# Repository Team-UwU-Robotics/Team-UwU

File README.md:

# Team-UwU
Official Repository for Team UwU

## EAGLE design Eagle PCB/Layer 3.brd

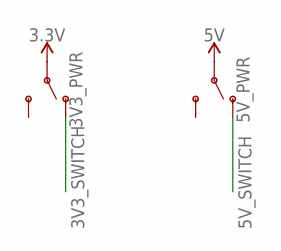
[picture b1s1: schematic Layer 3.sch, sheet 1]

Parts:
3V3_PWR, 5V_PWR: SWITCH-SPDT-PTH-11.6X4.0MM-LOCK; SWITCH_SPDT_PTH_11.6X4.0MM_LOCK

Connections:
3.3V: 3V3_PWR.2; also elsewhere on the board
3V3_SWITCH: 3V3_PWR.1 (O); also elsewhere on the board
5V_SWITCH: 5V_PWR.1 (O); also elsewhere on the board

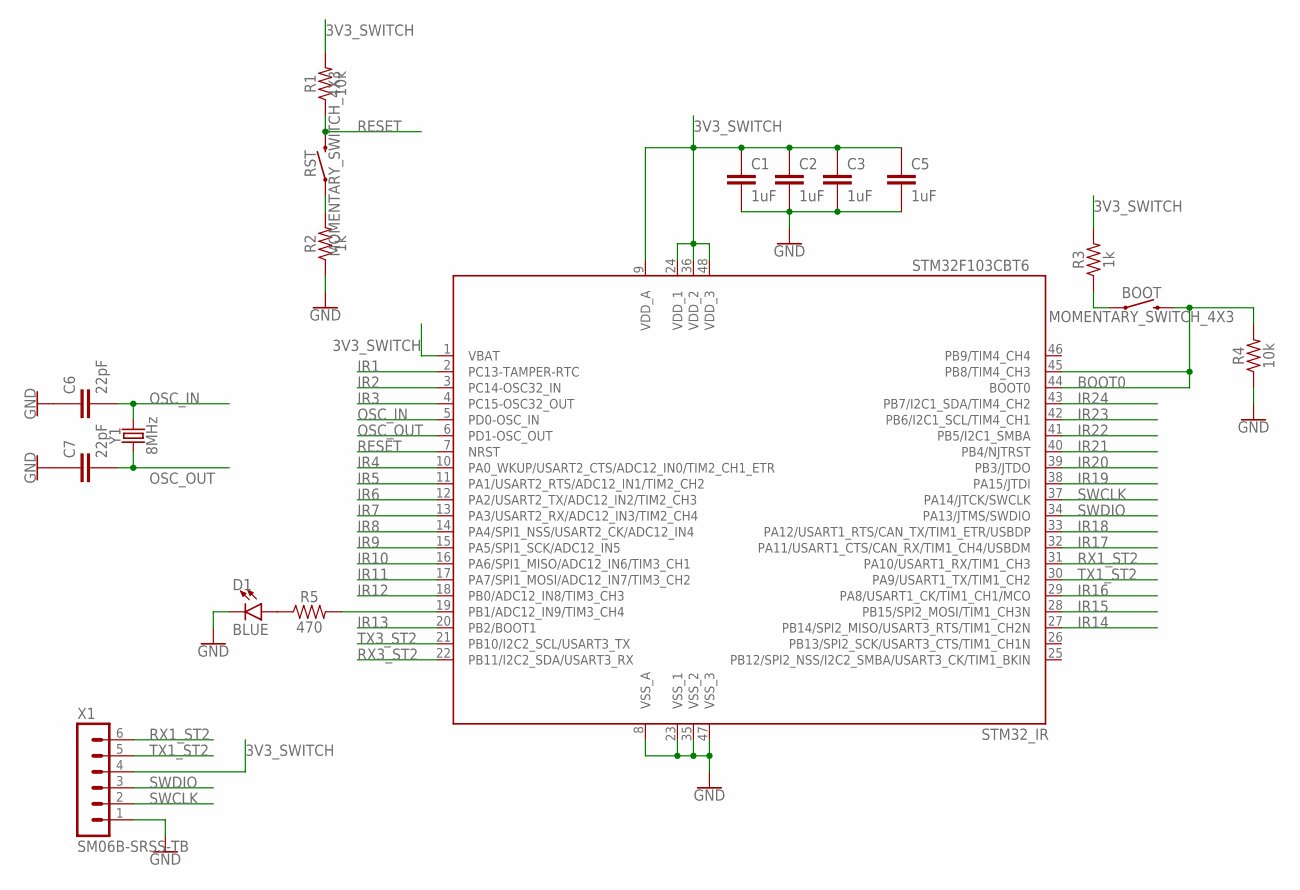
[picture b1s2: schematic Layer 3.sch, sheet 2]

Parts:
BOOT: MOMENTARY_SWITCH_4X3
C1, C2, C3, C5: 1uF; C0603
C6, C7: 22pF; C0603
D1: BLUE; LED-0603
R1, R4: 10k; R0603
R2, R3: 1k; R0603
R5: 470; R0603
RST: MOMENTARY_SWITCH_4X3
STM32_IR: STM32F103CBT6; LQFP48
X1: SM06B-SRSS-TB
Y1: 8MHz; CRYSTAL-SMD-5X3.2-2PAD

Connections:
3V3_SWITCH: C1.1, C2.1, C3.1, C5.2, R1.2, R3.2, STM32_IR.1 (VBAT), STM32_IR.9 (VDD_A), STM32_IR.24 (VDD_1), STM32_IR.36 (VDD_2), STM32_IR.48 (VDD_3), X1.4; also elsewhere on the board
BOOT0: BOOT.P$2 (2), R4.2, STM32_IR.44 (BOOT0), STM32_IR.45 (PB8/TIM4_CH3)
GND: C1.2, C2.2, C3.2, C5.1, C6.1, C7.1, D1.C, R2.1, R4.1, STM32_IR.8 (VSS_A), STM32_IR.23 (VSS_1), STM32_IR.35 (VSS_2), STM32_IR.47 (VSS_3), X1.1; also elsewhere on the board
IR1: STM32_IR.2 (PC13-TAMPER-RTC); also elsewhere on the board
IR2: STM32_IR.3 (PC14-OSC32_IN); also elsewhere on the board
IR3: STM32_IR.4 (PC15-OSC32_OUT); also elsewhere on the board
IR4: STM32_IR.10 (PA0_WKUP/USART2_CTS/ADC12_IN0/TIM2_CH1_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); also elsewhere on the board
IR5: STM32_IR.11 (PA1/USART2_RTS/ADC12_IN1/TIM2_CH2); also elsewhere on the board
IR6: STM32_IR.12 (PA2/USART2_TX/ADC12_IN2/TIM2_CH3); also elsewhere on the board
IR7: STM32_IR.13 (PA3/USART2_RX/ADC12_IN3/TIM2_CH4); also elsewhere on the board
IR8: STM32_IR.14 (PA4/SPI1_NSS/USART2_CK/ADC12_IN4); also elsewhere on the board
IR9: STM32_IR.15 (PA5/SPI1_SCK/ADC12_IN5); also elsewhere on the board
IR10: STM32_IR.16 (PA6/SPI1_MISO/ADC12_IN6/TIM3_CH1); also elsewhere on the board
IR11: STM32_IR.17 (PA7/SPI1_MOSI/ADC12_IN7/TIM3_CH2); also elsewhere on the board
IR12: STM32_IR.18 (PB0/ADC12_IN8/TIM3_CH3); also elsewhere on the board
IR13: STM32_IR.20 (PB2/BOOT1); also elsewhere on the board
IR14: STM32_IR.27 (PB14/SPI2_MISO/USART3_RTS/TIM1_CH2N); also elsewhere on the board
IR15: STM32_IR.28 (PB15/SPI2_MOSI/TIM1_CH3N); also elsewhere on the board
IR16: STM32_IR.29 (PA8/USART1_CK/TIM1_CH1/MCO); also elsewhere on the board
IR17: STM32_IR.32 (PA11/USART1_CTS/CAN_RX/TIM1_CH4/USBDM); also elsewhere on the board
IR18: STM32_IR.33 (PA12/USART1_RTS/CAN_TX/TIM1_ETR/USBDP); also elsewhere on the board
IR19: STM32_IR.38 (PA15/JTDI); also elsewhere on the board
IR20: STM32_IR.39 (PB3/JTDO); also elsewhere on the board
IR21: STM32_IR.40 (PB4/NJTRST); also elsewhere on the board
IR22: STM32_IR.41 (PB5/I2C1_SMBA); also elsewhere on the board
IR23: STM32_IR.42 (PB6/I2C1_SCL/TIM4_CH1); also elsewhere on the board
IR24: STM32_IR.43 (PB7/I2C1_SDA/TIM4_CH2); also elsewhere on the board
unnamed: R2.2, RST.P$1 (1)
unnamed: BOOT.P$1 (1), R3.1
unnamed: R5.2, STM32_IR.19 (PB1/ADC12_IN9/TIM3_CH4)
unnamed: D1.A, R5.1
OSC_IN: C6.2, STM32_IR.5 (PD0-OSC_IN), Y1.P$2 (2)
OSC_OUT: C7.2, STM32_IR.6 (PD1-OSC_OUT), Y1.P$1 (1)
RESET: R1.1, RST.P$2 (2), STM32_IR.7 (NRST)
RX1_ST2: STM32_IR.31 (PA10/USART1_RX/TIM1_CH3), X1.6; also elsewhere on the board
RX3_ST2: STM32_IR.22 (PB11/I2C2_SDA/USART3_RX)
SWCLK: STM32_IR.37 (PA14/JTCK/SWCLK), X1.2
SWDIO: STM32_IR.34 (PA13/JTMS/SWDIO), X1.3
TX1_ST2: STM32_IR.30 (PA9/USART1_TX/TIM1_CH2), X1.5; also elsewhere on the board
TX3_ST2: STM32_IR.21 (PB10/I2C2_SCL/USART3_TX)

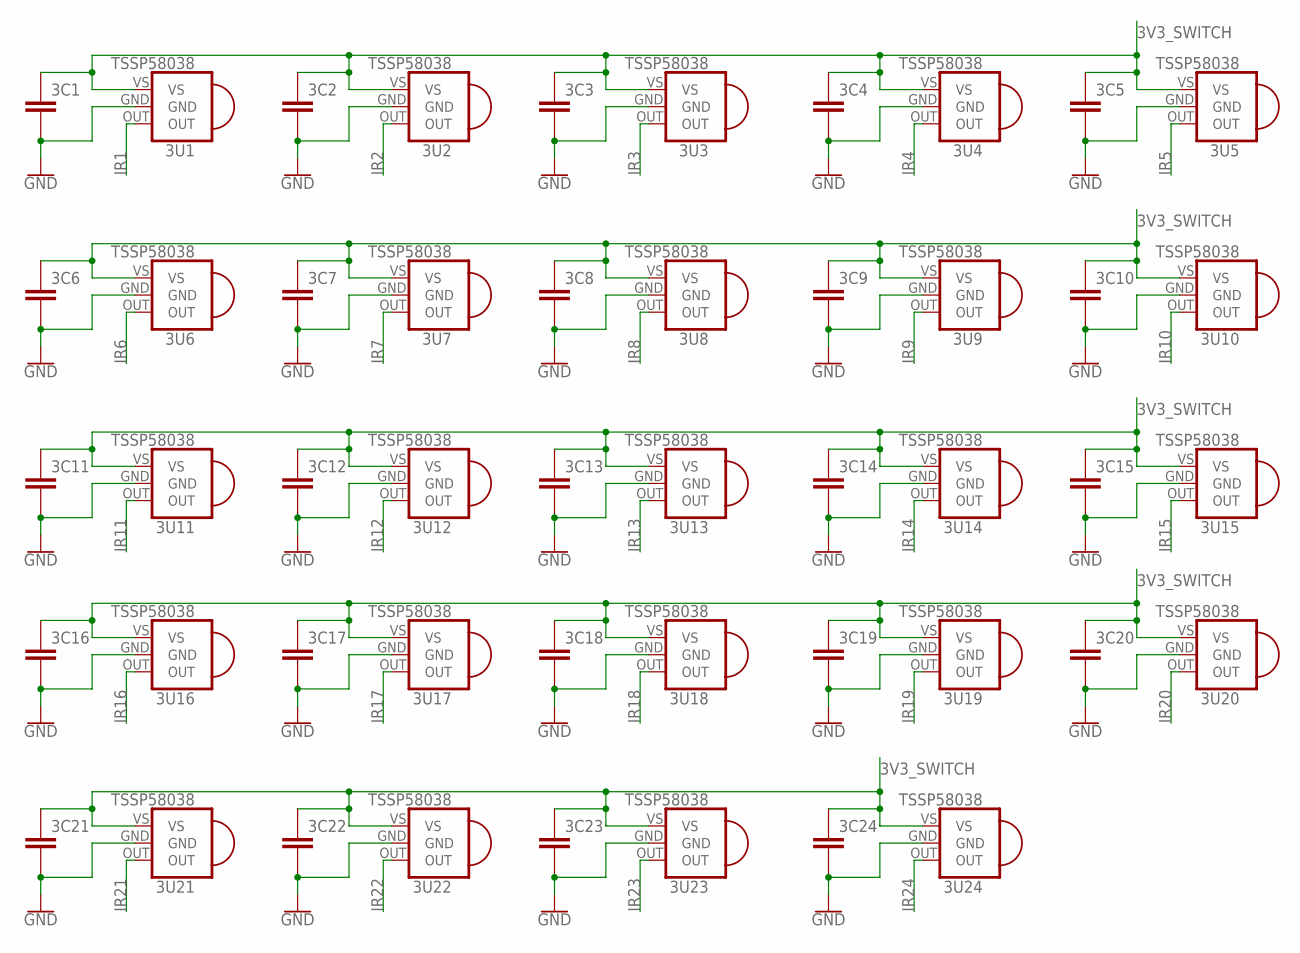
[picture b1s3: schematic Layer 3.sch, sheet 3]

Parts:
3C1, 3C2, 3C3, 3C4, 3C5, 3C6, 3C7, 3C8, 3C9, 3C10, 3C11, 3C12, 3C13, 3C14, 3C15, 3C16, 3C17, 3C18, 3C19, 3C20, 3C21, 3C22, 3C23, 3C24: CAPACITOR0603; C0603
3U1, 3U2, 3U3, 3U4, 3U5, 3U6, 3U7, 3U8, 3U9, 3U10, 3U11, 3U12, 3U13, 3U14, 3U15, 3U16, 3U17, 3U18, 3U19, 3U20, 3U21, 3U22, 3U23, 3U24: TSSP58038

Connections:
3V3_SWITCH: 3C1.1, 3C2.1, 3C3.1, 3C4.1, 3C5.1, 3C6.1, 3C7.1, 3C8.1, 3C9.1, 3C10.1, 3C11.1, 3C12.1, 3C13.1, 3C14.1, 3C15.1, 3C16.1, 3C17.1, 3C18.1, 3C19.1, 3C20.1, 3C21.1, 3C22.1, 3C23.1, 3C24.1, 3U1.VS, 3U2.VS, 3U3.VS, 3U4.VS, 3U5.VS, 3U6.VS, 3U7.VS, 3U8.VS, 3U9.VS, 3U10.VS, 3U11.VS, 3U12.VS, 3U13.VS, 3U14.VS, 3U15.VS, 3U16.VS, 3U17.VS, 3U18.VS, 3U19.VS, 3U20.VS, 3U21.VS, 3U22.VS, 3U23.VS, 3U24.VS; also elsewhere on the board
GND: 3C1.2, 3C2.2, 3C3.2, 3C4.2, 3C5.2, 3C6.2, 3C7.2, 3C8.2, 3C9.2, 3C10.2, 3C11.2, 3C12.2, 3C13.2, 3C14.2, 3C15.2, 3C16.2, 3C17.2, 3C18.2, 3C19.2, 3C20.2, 3C21.2, 3C22.2, 3C23.2, 3C24.2, 3U1.GND, 3U2.GND, 3U3.GND, 3U4.GND, 3U5.GND, 3U6.GND, 3U7.GND, 3U8.GND, 3U9.GND, 3U10.GND, 3U11.GND, 3U12.GND, 3U13.GND, 3U14.GND, 3U15.GND, 3U16.GND, 3U17.GND, 3U18.GND, 3U19.GND, 3U20.GND, 3U21.GND, 3U22.GND, 3U23.GND, 3U24.GND; also elsewhere on the board
IR1: 3U1.OUT; also elsewhere on the board
IR2: 3U2.OUT; also elsewhere on the board
IR3: 3U3.OUT; also elsewhere on the board
IR4: 3U4.OUT; also elsewhere on the board
IR5: 3U5.OUT; also elsewhere on the board
IR6: 3U6.OUT; also elsewhere on the board
IR7: 3U7.OUT; also elsewhere on the board
IR8: 3U8.OUT; also elsewhere on the board
IR9: 3U9.OUT; also elsewhere on the board
IR10: 3U10.OUT; also elsewhere on the board
IR11: 3U11.OUT; also elsewhere on the board
IR12: 3U12.OUT; also elsewhere on the board
IR13: 3U13.OUT; also elsewhere on the board
IR14: 3U14.OUT; also elsewhere on the board
IR15: 3U15.OUT; also elsewhere on the board
IR16: 3U16.OUT; also elsewhere on the board
IR17: 3U17.OUT; also elsewhere on the board
IR18: 3U18.OUT; also elsewhere on the board
IR19: 3U19.OUT; also elsewhere on the board
IR20: 3U20.OUT; also elsewhere on the board
IR21: 3U21.OUT; also elsewhere on the board
IR22: 3U22.OUT; also elsewhere on the board
IR23: 3U23.OUT; also elsewhere on the board
IR24: 3U24.OUT; also elsewhere on the board

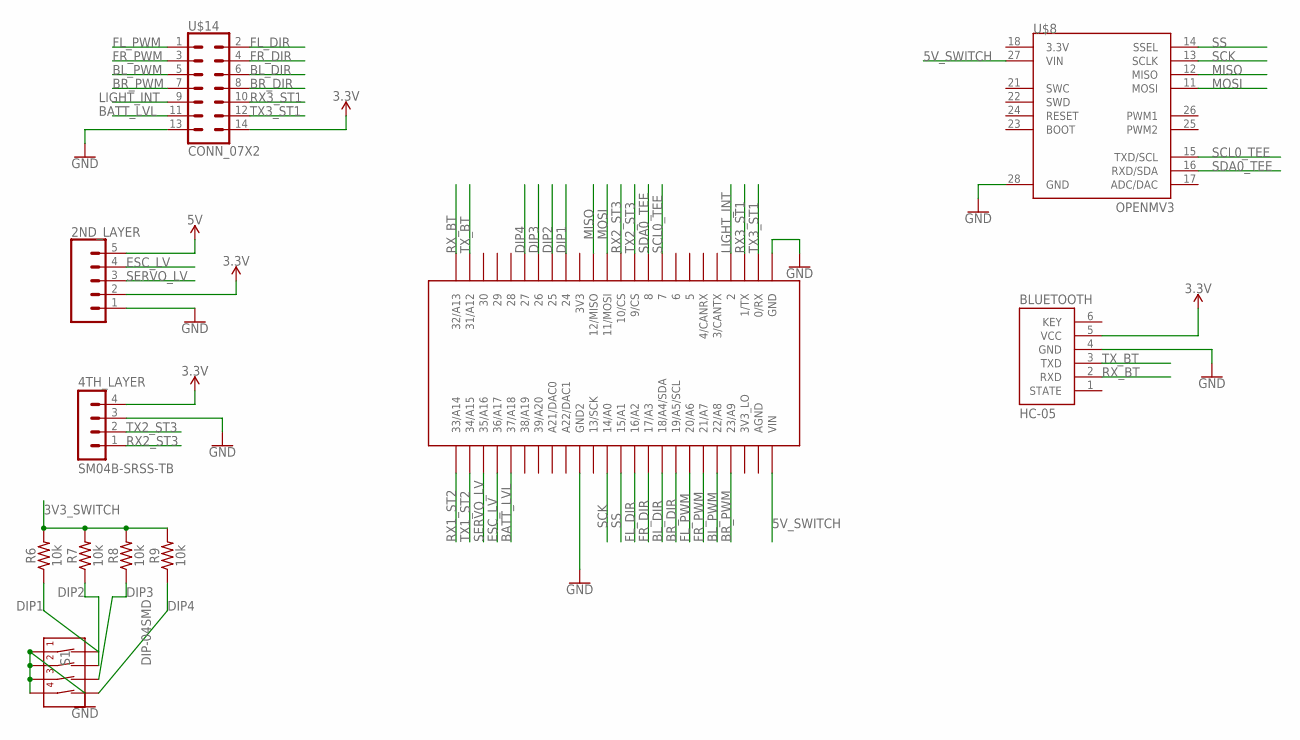
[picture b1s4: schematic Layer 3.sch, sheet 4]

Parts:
2ND_LAYER: CONN_05LOCK; 1X05_LOCK
4TH_LAYER: SM04B-SRSS-TB
BLUETOOTH: HC-05
R6, R7, R8, R9: 10k; R0603
S1: DIP-04SMD; DIPSWITCH-04-SMD
U$1: TEENSY_3.5/3.6_NO_MIDDLE
U$8: OPENMV3
U$14: CONN_07X2; 2X7

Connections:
3.3V: 2ND_LAYER.2, 4TH_LAYER.4, BLUETOOTH.5 (VCC), U$14.14; also elsewhere on the board
3V3_SWITCH: R6.2, R7.2, R8.2, R9.2; also elsewhere on the board
5V_SWITCH: U$1.VIN, U$8.27 (VIN); also elsewhere on the board
BATT_LVL: U$1.37/A18, U$14.11
BL_DIR: U$1.18/A4/SDA, U$14.6
BL_PWM: U$1.22/A8, U$14.5
BR_DIR: U$1.19/A5/SCL, U$14.8
BR_PWM: U$1.23/A9, U$14.7
DIP1: R6.1, S1.1 (1A), U$1.24
DIP2: R7.1, S1.2 (2A), U$1.25
DIP3: R8.1, S1.3 (3A), U$1.26
DIP4: R9.1, S1.4 (4A), U$1.27
FL_DIR: U$1.16/A2, U$14.2
FL_PWM: U$1.20/A6, U$14.1
FR_DIR: U$1.17/A3, U$14.4
FR_PWM: U$1.21/A7, U$14.3
GND: 2ND_LAYER.1, 4TH_LAYER.3, BLUETOOTH.4 (GND), S1.5 (4B), S1.6 (3B), S1.7 (2B), S1.8 (1B), U$1.GND2, U$8.28 (GND), U$14.13; also elsewhere on the board
LIGHT_INT: U$1.2, U$14.9
MISO: U$1.12/MISO, U$8.12 (MISO)
MOSI: U$1.11/MOSI, U$8.11 (MOSI)
RX1_ST2: U$1.33/A14; also elsewhere on the board
RX2_ST3: 4TH_LAYER.1, U$1.10/CS
RX3_ST1: U$1.1/TX, U$14.10
RX_BT: BLUETOOTH.2 (RXD), U$1.32/A13
SCK: U$1.14/A0, U$8.13 (SCLK)
SCL0_TEE: U$1.7, U$8.15 (TXD/SCL)
SDA0_TEE: U$1.8, U$8.16 (RXD/SDA)
SERVO_LV: 2ND_LAYER.3, U$1.35/A16; also elsewhere on the board
SS: U$1.15/A1, U$8.14 (SSEL)
TX1_ST2: U$1.34/A15; also elsewhere on the board
TX2_ST3: 4TH_LAYER.2, U$1.9/CS
TX3_ST1: U$1.0/RX, U$14.12
TX_BT: BLUETOOTH.3 (TXD), U$1.31/A12

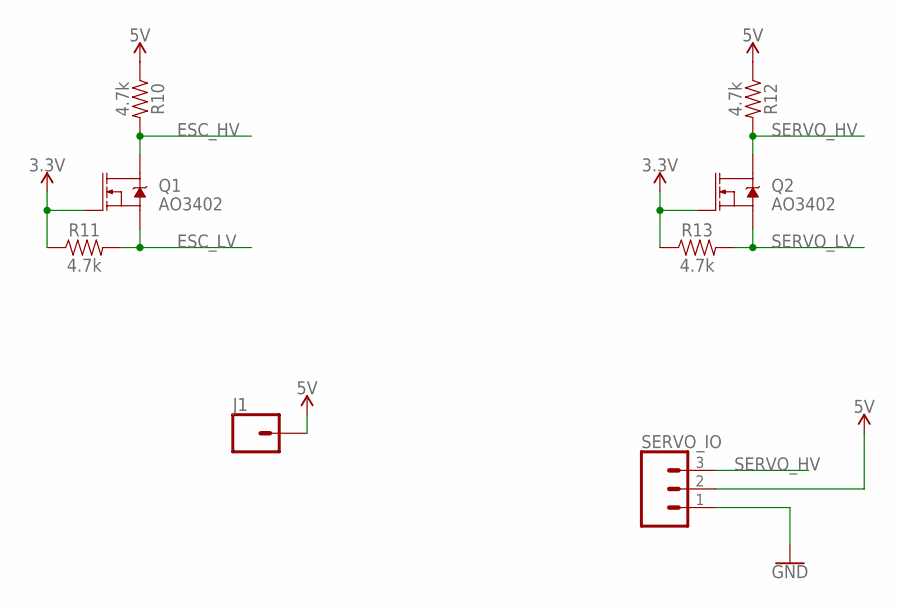
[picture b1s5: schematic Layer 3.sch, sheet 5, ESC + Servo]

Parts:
J1: CONN_01; 1X01
Q1, Q2: AO3402; SOT23-3
R10, R11, R12, R13: 4.7k; R0603
SERVO_IO: CONN_03LOCK; 1X03_LOCK

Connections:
3.3V: Q1.1 (G), Q2.1 (G), R11.1, R13.1; also elsewhere on the board
GND: SERVO_IO.1; also elsewhere on the board
unnamed: Q1.2 (S), R11.2
unnamed: Q1.3 (D), R10.2
SERVO_HV: Q2.3 (D), R12.2, SERVO_IO.3
SERVO_LV: Q2.2 (S), R13.2; also elsewhere on the board

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
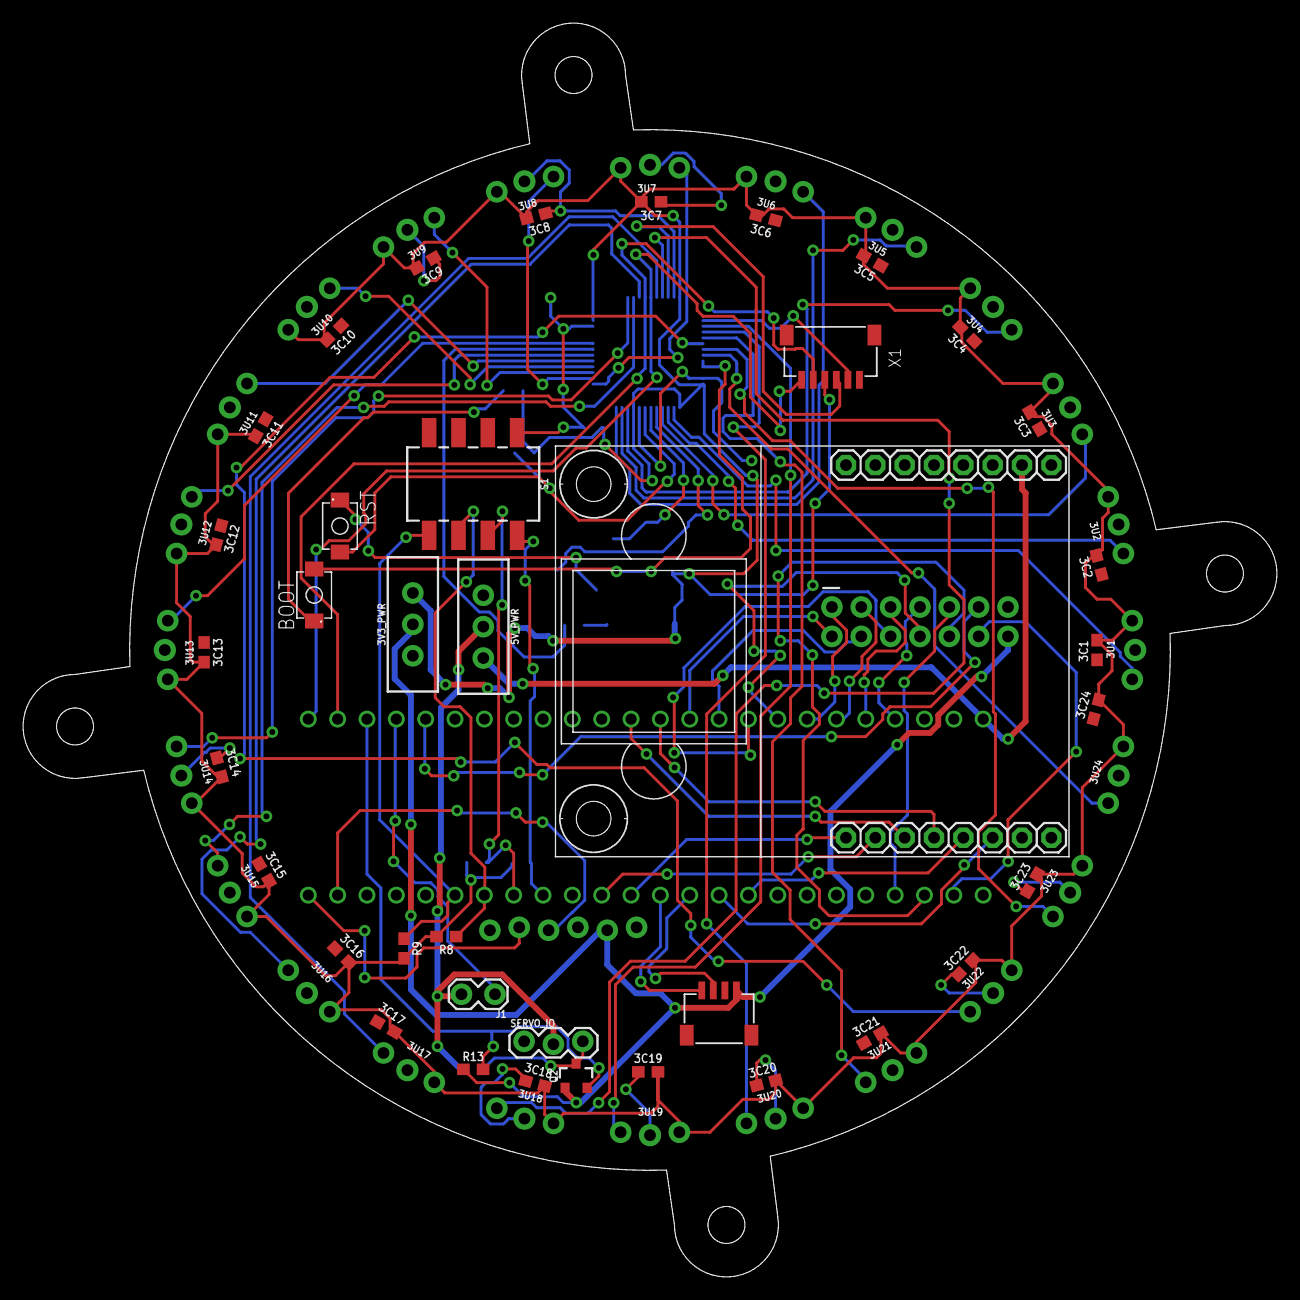
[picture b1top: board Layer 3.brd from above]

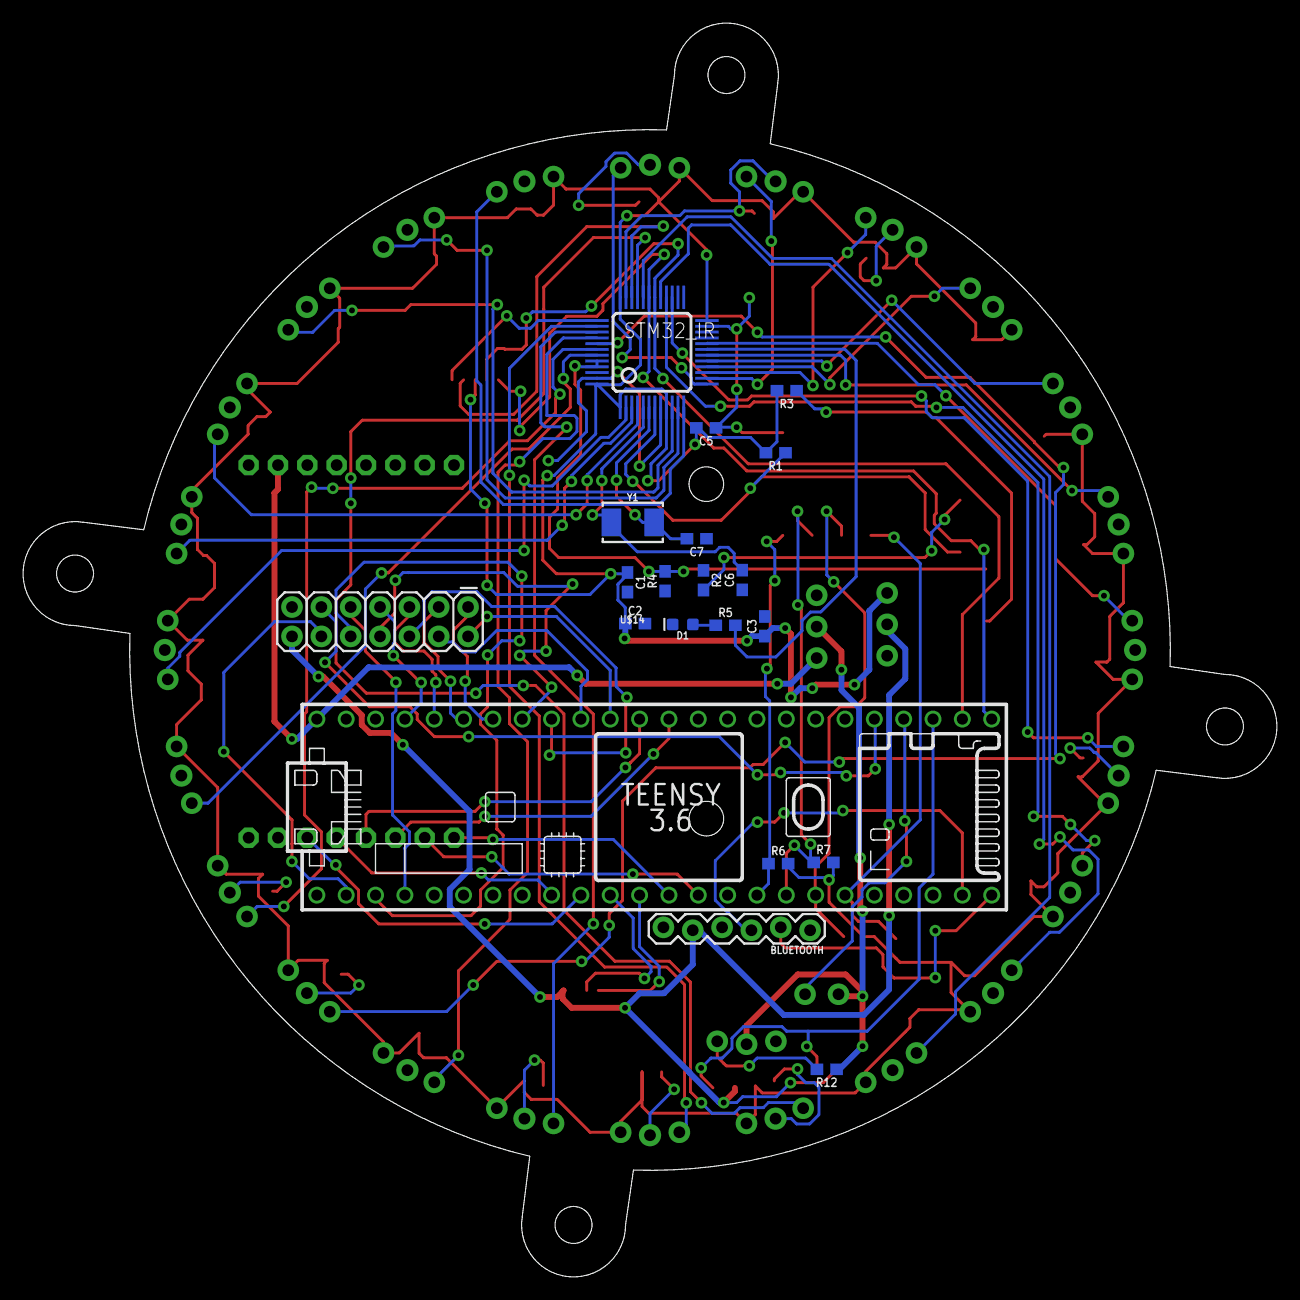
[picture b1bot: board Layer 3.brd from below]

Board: 2 copper layers, 108.5 x 108.5 mm, 82 parts (20 on the bottom side), 70 nets.

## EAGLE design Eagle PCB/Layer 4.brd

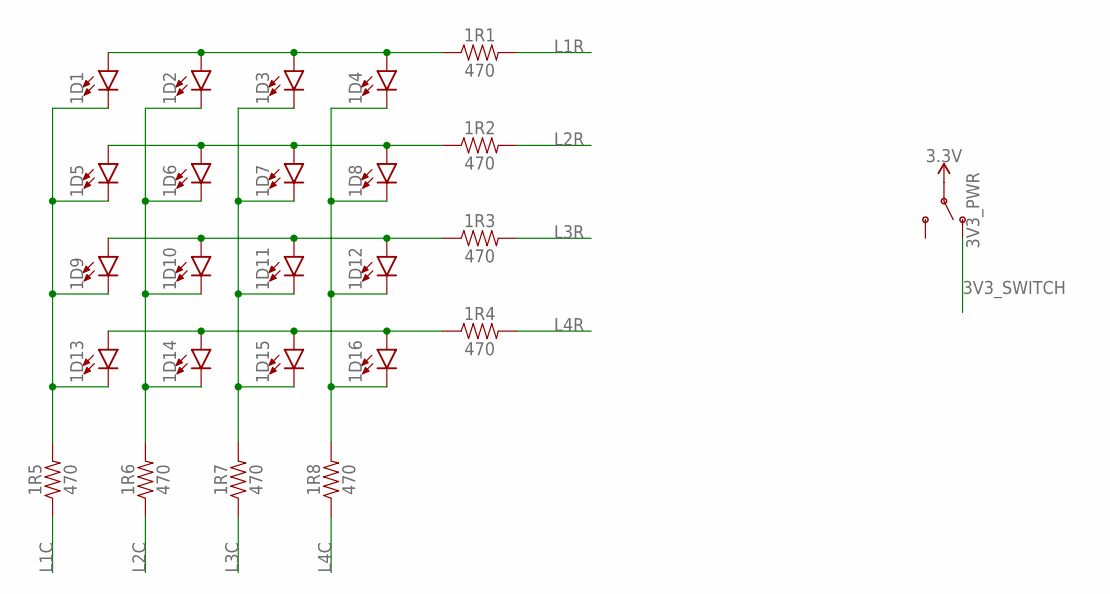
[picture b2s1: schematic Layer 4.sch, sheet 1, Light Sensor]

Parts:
1D1, 1D2, 1D3, 1D4, 1D5, 1D6, 1D7, 1D8, 1D9, 1D10, 1D11, 1D12, 1D13, 1D14, 1D15, 1D16: LED0603; LED-0603
1R1, 1R2, 1R3, 1R4, 1R5, 1R6, 1R7, 1R8: 470; R0603
3V3_PWR: SWITCH-SPDT-PTH-11.6X4.0MM-LOCK; SWITCH_SPDT_PTH_11.6X4.0MM_LOCK

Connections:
3.3V: 3V3_PWR.2; also elsewhere on the board
3V3_SWITCH: 3V3_PWR.1 (O); also elsewhere on the board
L1C: 1R5.1; also elsewhere on the board
L1R: 1R1.2; also elsewhere on the board
L2C: 1R6.1; also elsewhere on the board
L2R: 1R2.2; also elsewhere on the board
L3C: 1R7.1; also elsewhere on the board
L3R: 1R3.2; also elsewhere on the board
L4C: 1R8.1; also elsewhere on the board
L4R: 1R4.2; also elsewhere on the board
unnamed: 1D1.A, 1D2.A, 1D3.A, 1D4.A, 1R1.1
unnamed: 1D1.C, 1D5.C, 1D9.C, 1D13.C, 1R5.2
unnamed: 1D5.A, 1D6.A, 1D7.A, 1D8.A, 1R2.1
unnamed: 1D9.A, 1D10.A, 1D11.A, 1D12.A, 1R3.1
unnamed: 1D13.A, 1D14.A, 1D15.A, 1D16.A, 1R4.1
unnamed: 1D2.C, 1D6.C, 1D10.C, 1D14.C, 1R6.2
unnamed: 1D3.C, 1D7.C, 1D11.C, 1D15.C, 1R7.2
unnamed: 1D4.C, 1D8.C, 1D12.C, 1D16.C, 1R8.2

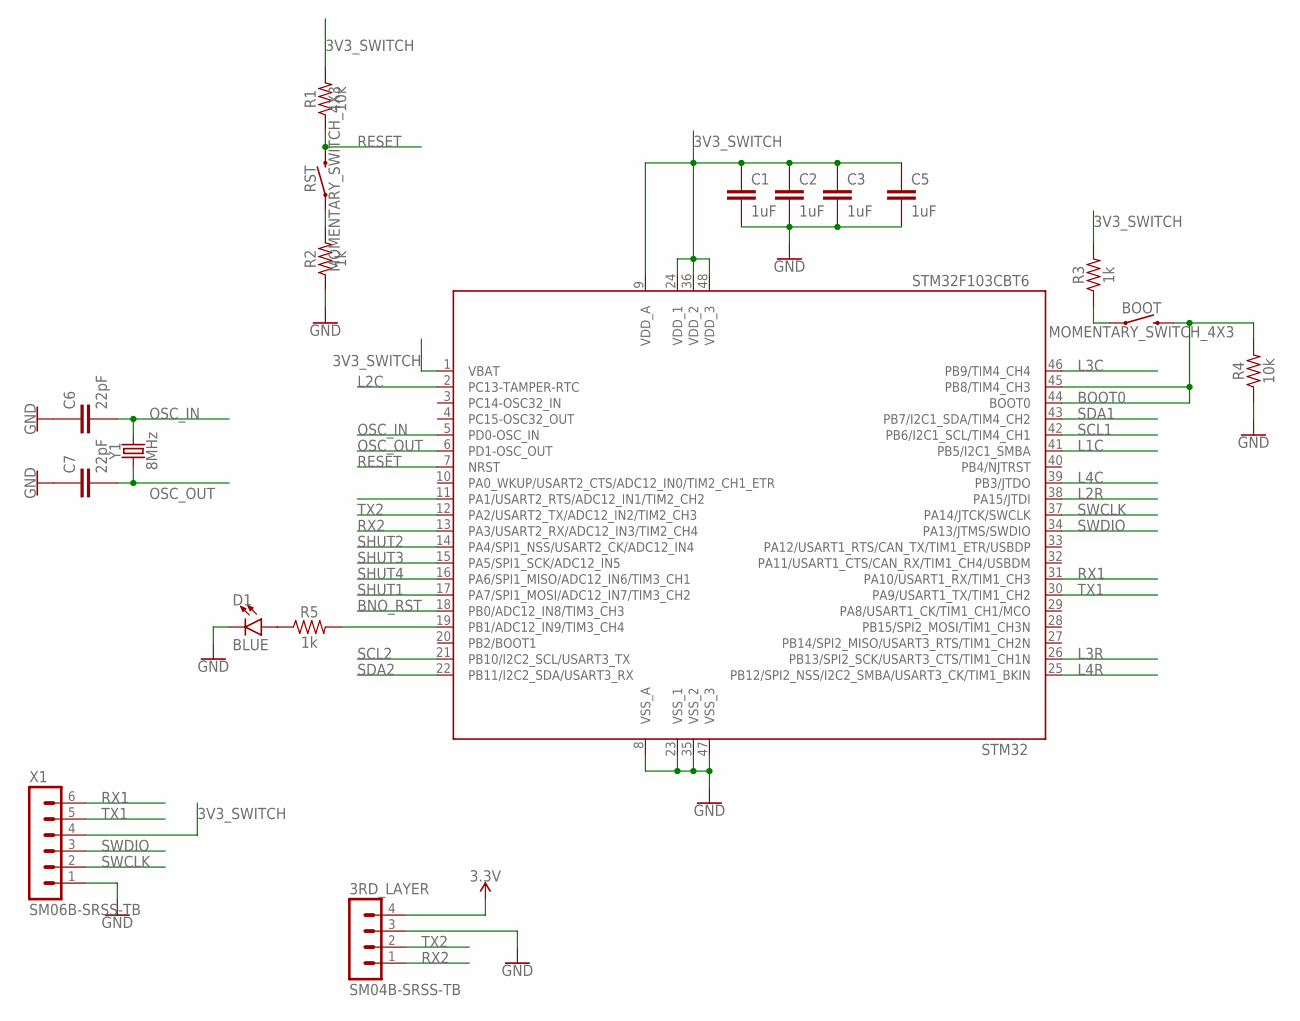
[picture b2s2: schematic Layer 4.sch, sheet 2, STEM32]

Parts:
3RD_LAYER: SM04B-SRSS-TB
BOOT: MOMENTARY_SWITCH_4X3
C1, C2, C3, C5: 1uF; C0603
C6, C7: 22pF; C0603
D1: BLUE; LED-0603
R1, R4: 10k; R0603
R2, R3, R5: 1k; R0603
RST: MOMENTARY_SWITCH_4X3
STM32: STM32F103CBT6; LQFP48
X1: SM06B-SRSS-TB
Y1: 8MHz; CRYSTAL-SMD-5X3.2-2PAD

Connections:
3.3V: 3RD_LAYER.4; also elsewhere on the board
3V3_SWITCH: C1.1, C2.1, C3.1, C5.2, R1.2, R3.2, STM32.1 (VBAT), STM32.9 (VDD_A), STM32.24 (VDD_1), STM32.36 (VDD_2), STM32.48 (VDD_3), X1.4; also elsewhere on the board
BNO_RST: STM32.18 (PB0/ADC12_IN8/TIM3_CH3); also elsewhere on the board
BOOT0: BOOT.P$2 (2), R4.2, STM32.44 (BOOT0), STM32.45 (PB8/TIM4_CH3)
GND: 3RD_LAYER.3, C1.2, C2.2, C3.2, C5.1, C6.1, C7.1, D1.C, R2.1, R4.1, STM32.8 (VSS_A), STM32.23 (VSS_1), STM32.35 (VSS_2), STM32.47 (VSS_3), X1.1; also elsewhere on the board
L1C: STM32.41 (PB5/I2C1_SMBA); also elsewhere on the board
L1R: STM32.11 (PA1/USART2_RTS/ADC12_IN1/TIM2_CH2); also elsewhere on the board
L2C: STM32.2 (PC13-TAMPER-RTC); also elsewhere on the board
L2R: STM32.38 (PA15/JTDI); also elsewhere on the board
L3C: STM32.46 (PB9/TIM4_CH4); also elsewhere on the board
L3R: STM32.26 (PB13/SPI2_SCK/USART3_CTS/TIM1_CH1N); also elsewhere on the board
L4C: STM32.39 (PB3/JTDO); also elsewhere on the board
L4R: STM32.25 (PB12/SPI2_NSS/I2C2_SMBA/USART3_CK/TIM1_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); also elsewhere on the board
unnamed: R2.2, RST.P$1 (1)
unnamed: BOOT.P$1 (1), R3.1
unnamed: R5.2, STM32.19 (PB1/ADC12_IN9/TIM3_CH4)
unnamed: D1.A, R5.1
OSC_IN: C6.2, STM32.5 (PD0-OSC_IN), Y1.P$2 (2)
OSC_OUT: C7.2, STM32.6 (PD1-OSC_OUT), Y1.P$1 (1)
RESET: R1.1, RST.P$2 (2), STM32.7 (NRST)
RX1: STM32.31 (PA10/USART1_RX/TIM1_CH3), X1.6
RX2: 3RD_LAYER.1, STM32.13 (PA3/USART2_RX/ADC12_IN3/TIM2_CH4)
SCL1: STM32.42 (PB6/I2C1_SCL/TIM4_CH1); also elsewhere on the board
SCL2: STM32.21 (PB10/I2C2_SCL/USART3_TX); also elsewhere on the board
SDA1: STM32.43 (PB7/I2C1_SDA/TIM4_CH2); also elsewhere on the board
SDA2: STM32.22 (PB11/I2C2_SDA/USART3_RX); also elsewhere on the board
SHUT1: STM32.17 (PA7/SPI1_MOSI/ADC12_IN7/TIM3_CH2); also elsewhere on the board
SHUT2: STM32.14 (PA4/SPI1_NSS/USART2_CK/ADC12_IN4); also elsewhere on the board
SHUT3: STM32.15 (PA5/SPI1_SCK/ADC12_IN5); also elsewhere on the board
SHUT4: STM32.16 (PA6/SPI1_MISO/ADC12_IN6/TIM3_CH1); also elsewhere on the board
SWCLK: STM32.37 (PA14/JTCK/SWCLK), X1.2
SWDIO: STM32.34 (PA13/JTMS/SWDIO), X1.3
TX1: STM32.30 (PA9/USART1_TX/TIM1_CH2), X1.5
TX2: 3RD_LAYER.2, STM32.12 (PA2/USART2_TX/ADC12_IN2/TIM2_CH3)

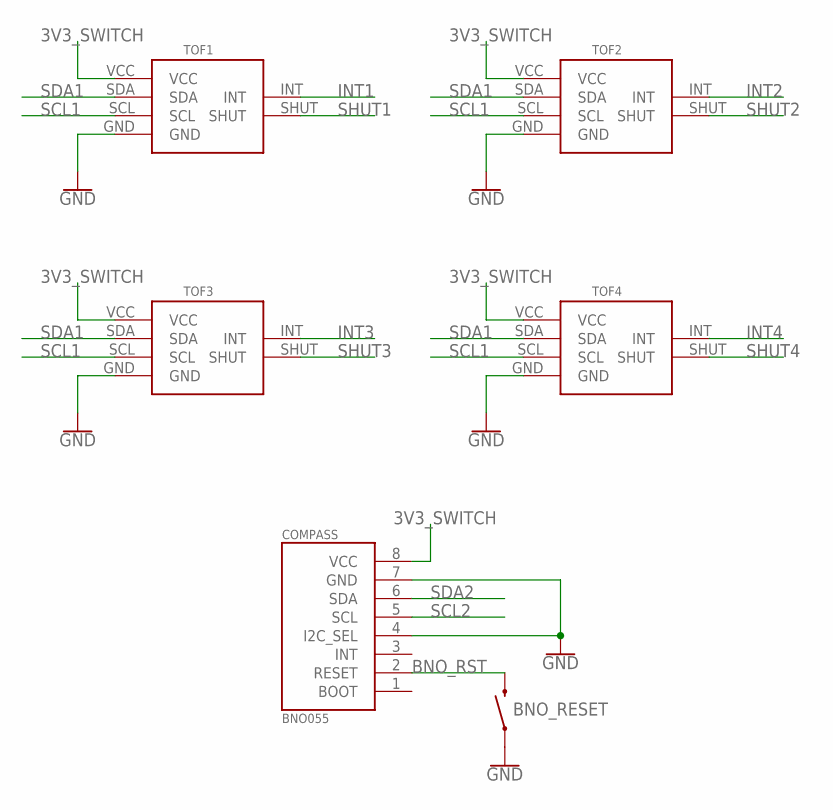
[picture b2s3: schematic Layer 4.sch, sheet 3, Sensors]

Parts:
BNO_RESET: MOMENTARY_SWITCH_4X3
COMPASS: BNO055
TOF1, TOF2, TOF3, TOF4: VL53L1X; VL53L1X_SLANTEDPINS

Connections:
3V3_SWITCH: COMPASS.8 (VCC), TOF1.VCC, TOF2.VCC, TOF3.VCC, TOF4.VCC; also elsewhere on the board
BNO_RST: BNO_RESET.P$2 (2), COMPASS.2 (RESET); also elsewhere on the board
GND: BNO_RESET.P$1 (1), COMPASS.4 (I2C_SEL), COMPASS.7 (GND), TOF1.GND, TOF2.GND, TOF3.GND, TOF4.GND; also elsewhere on the board
INT1: TOF1.INT
INT2: TOF2.INT
INT3: TOF3.INT
INT4: TOF4.INT
SCL1: TOF1.SCL, TOF2.SCL, TOF3.SCL, TOF4.SCL; also elsewhere on the board
SCL2: COMPASS.5 (SCL); also elsewhere on the board
SDA1: TOF1.SDA, TOF2.SDA, TOF3.SDA, TOF4.SDA; also elsewhere on the board
SDA2: COMPASS.6 (SDA); also elsewhere on the board
SHUT1: TOF1.SHUT; also elsewhere on the board
SHUT2: TOF2.SHUT; also elsewhere on the board
SHUT3: TOF3.SHUT; also elsewhere on the board
SHUT4: TOF4.SHUT; also elsewhere on the board

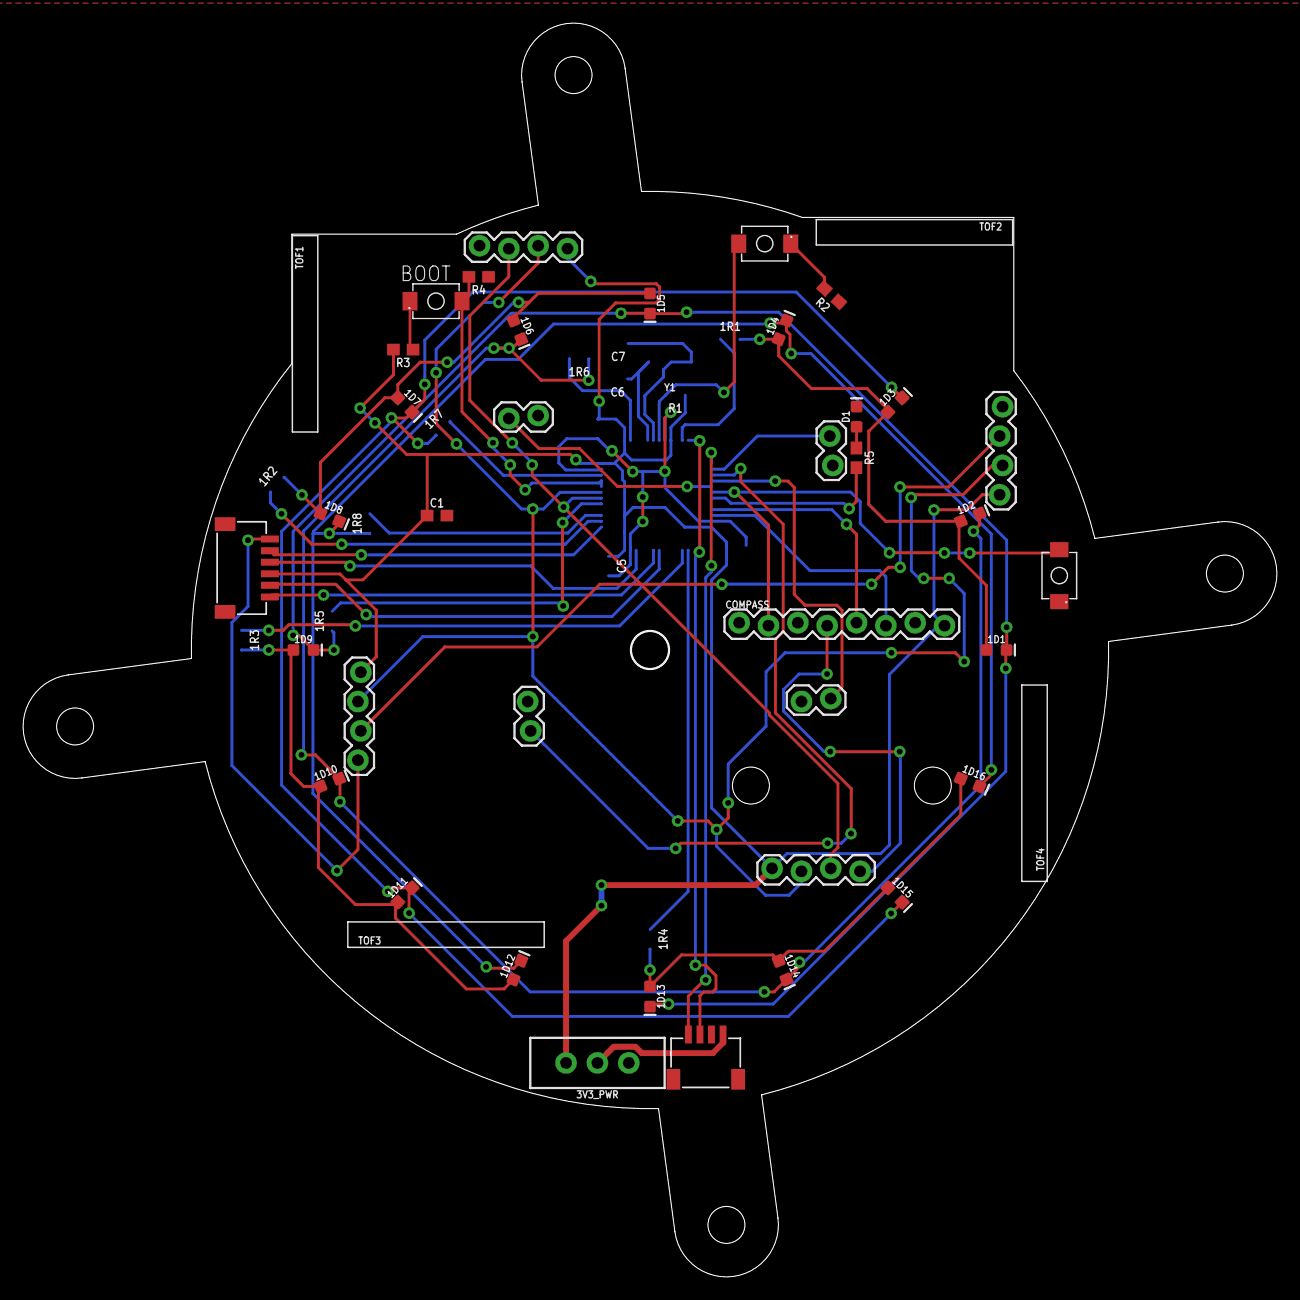
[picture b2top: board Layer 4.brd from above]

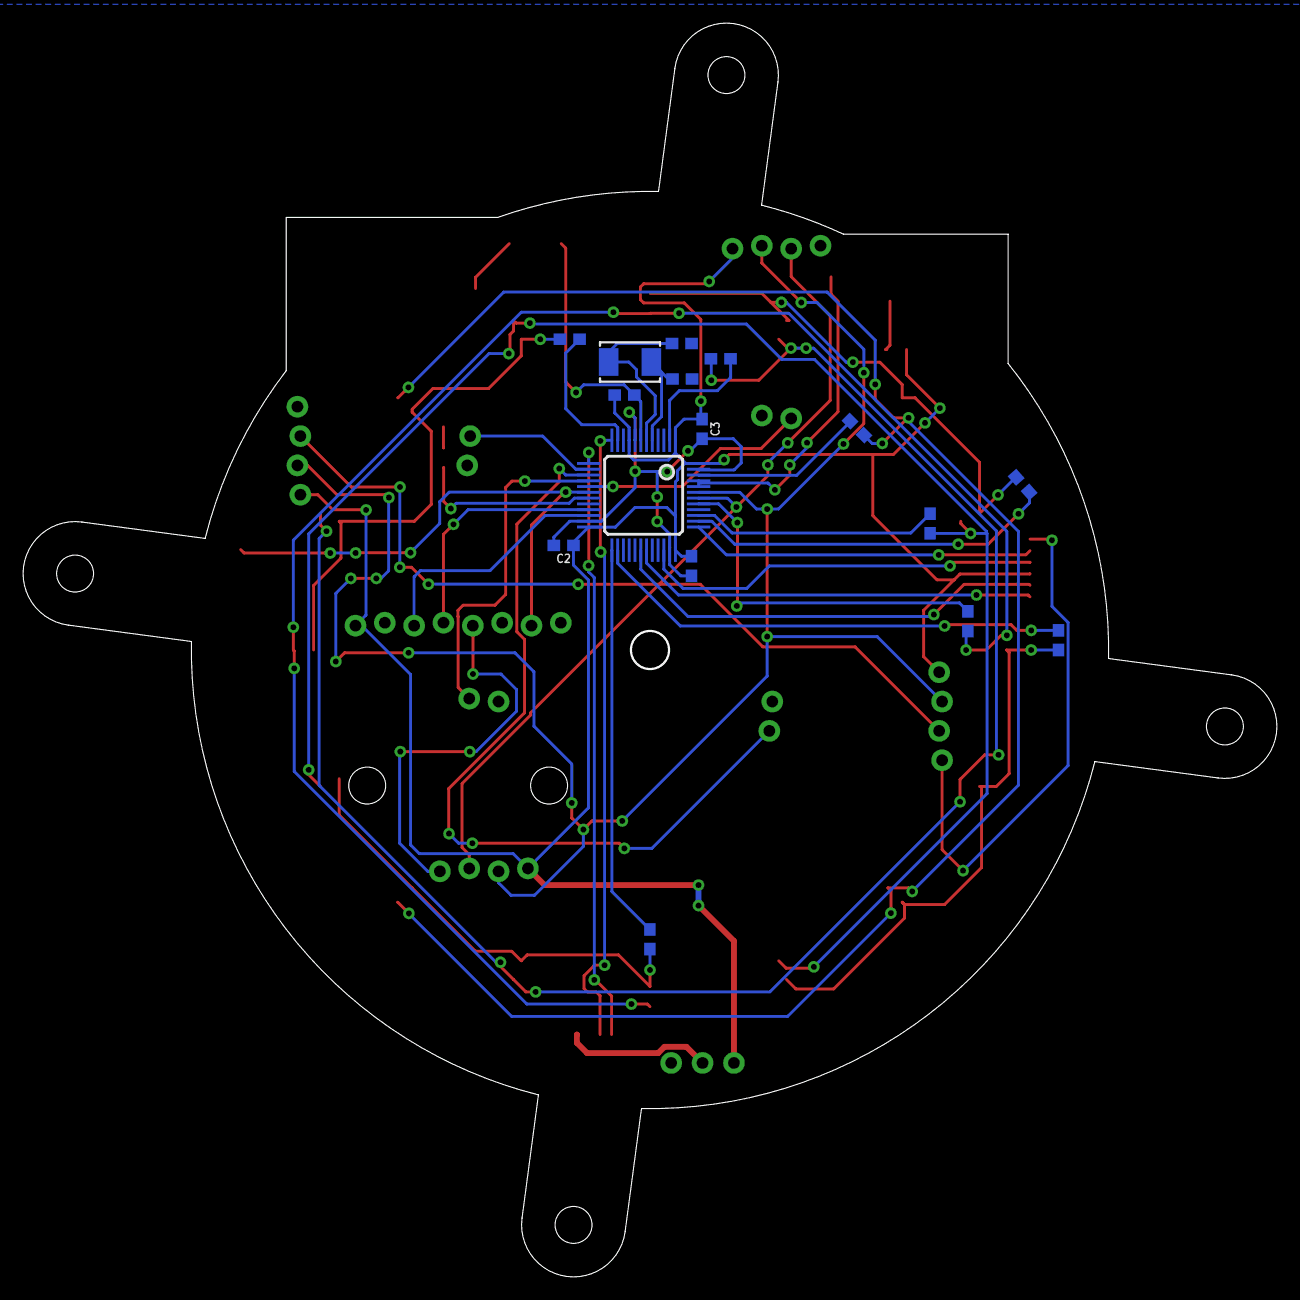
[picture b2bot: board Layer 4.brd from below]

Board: 2 copper layers, 108.5 x 108.5 mm, 49 parts (16 on the bottom side), 42 nets.

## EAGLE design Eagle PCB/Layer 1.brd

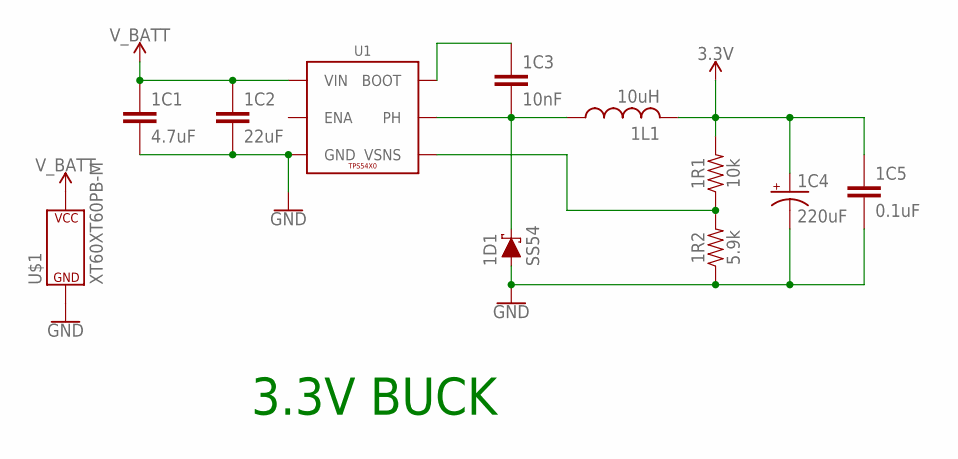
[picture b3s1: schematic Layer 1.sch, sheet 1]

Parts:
1C1: 4.7uF; C0603
1C2: 22uF; C1210
1C3: 10nF; C0603
1C4: 220uF; EIA7343
1C5: 0.1uF; C0603
1D1: SS54; SMA-DIODE
1L1: 10uH; SWPA8040
1R1: 10k; R0603
1R2: 5.9k; R0603
U1: TPS54X0; POWERPAD-SOIC-8
U$1: XT60XT60PB-M; XT60PB-M

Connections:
3.3V: 1C4.A (+), 1C5.1, 1L1.P2 (2), 1R1.2; also elsewhere on the board
GND: 1C1.2, 1C2.2, 1C4.C (-), 1C5.2, 1D1.A, 1R2.1, U1.6 (GND), U1.9 (GND), U1.P$1 (GND), U1.P$2 (GND), U1.P$3 (GND), U1.P$4 (GND), U1.P$5 (GND), U1.P$6 (GND), U$1.- (P$V-); also elsewhere on the board
unnamed: 1C3.1, U1.1 (BOOT)
unnamed: 1C3.2, 1D1.C, 1L1.P1 (1), U1.8 (PH)
unnamed: 1R1.1, 1R2.2, U1.4 (VSNS)
V_BATT: 1C1.1, 1C2.1, U1.7 (VIN), U$1.+ (P$V+); also elsewhere on the board

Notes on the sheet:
3.3V BUCK

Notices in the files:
parts and their libraries:
SparkFun-Capacitors: Licensing: Creative Commons ShareAlike 4.0 International - https://creativecommons.org/licenses/by-sa/4.0
